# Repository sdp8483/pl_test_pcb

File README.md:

prototype circuits that dont warrent a seperate repo. Mostly undocumented, enter at your own risk!

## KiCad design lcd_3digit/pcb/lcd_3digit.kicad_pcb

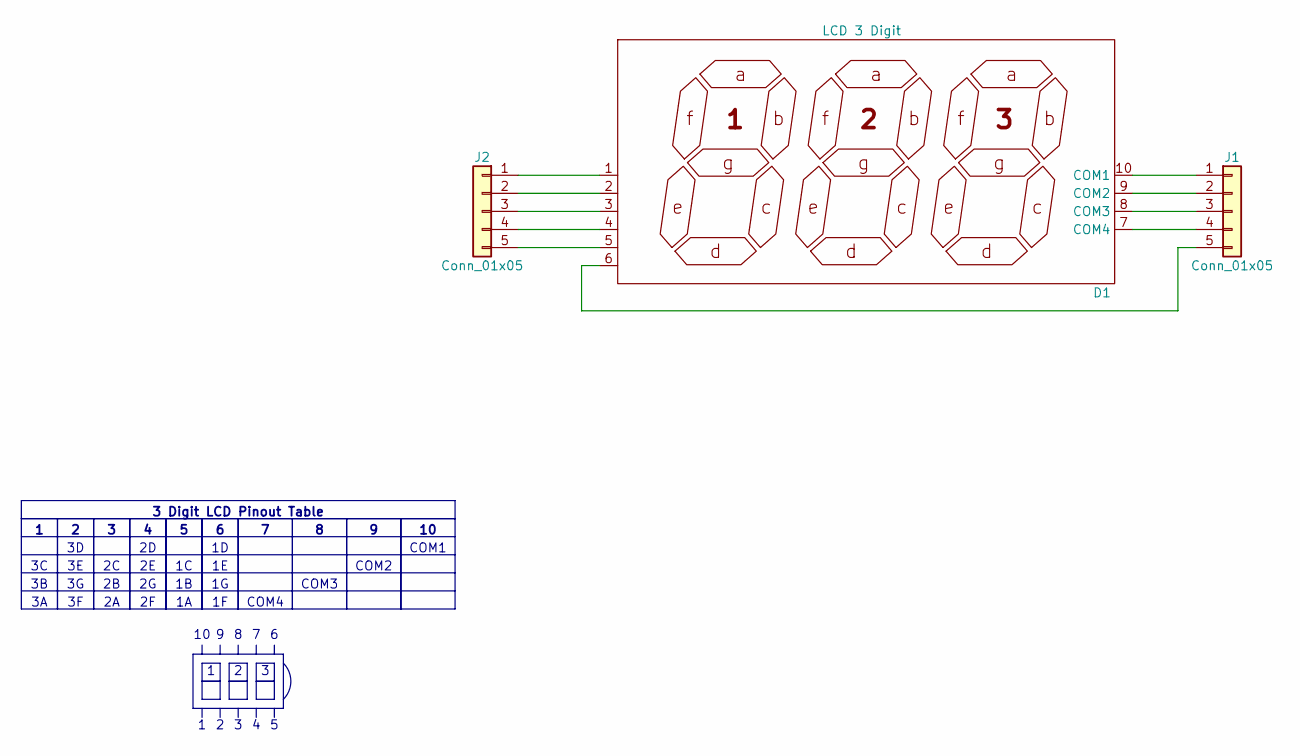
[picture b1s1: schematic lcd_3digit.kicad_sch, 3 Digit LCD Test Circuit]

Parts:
D1: LCD 3 Digit; LCD_3_Digit_10p
J1, J2: Conn_01x05; PinHeader_1x05_P2.54mm_Vertical

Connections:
unnamed: D1.10 (COM1), J1.1
unnamed: D1.9 (COM2), J1.2
unnamed: D1.8 (COM3), J1.3
unnamed: D1.7 (COM4), J1.4
unnamed: D1.6, J1.5
unnamed: D1.1, J2.1
unnamed: D1.2, J2.2
unnamed: D1.3, J2.3
unnamed: D1.4, J2.4
unnamed: D1.5, J2.5

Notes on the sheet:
COM1
COM3
COM2
COM4
3 Digit LCD Pinout Table

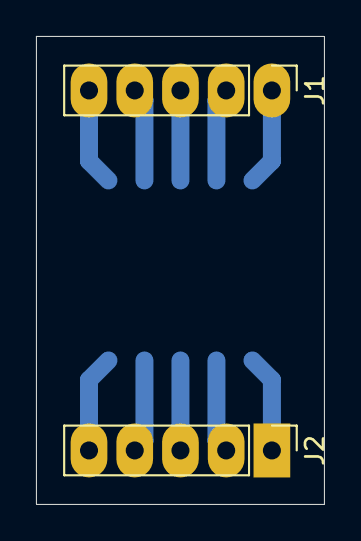
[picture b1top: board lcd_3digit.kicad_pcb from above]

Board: 2 copper layers, 16.0 x 26.0 mm, 3 parts (1 on the bottom side), 10 nets.

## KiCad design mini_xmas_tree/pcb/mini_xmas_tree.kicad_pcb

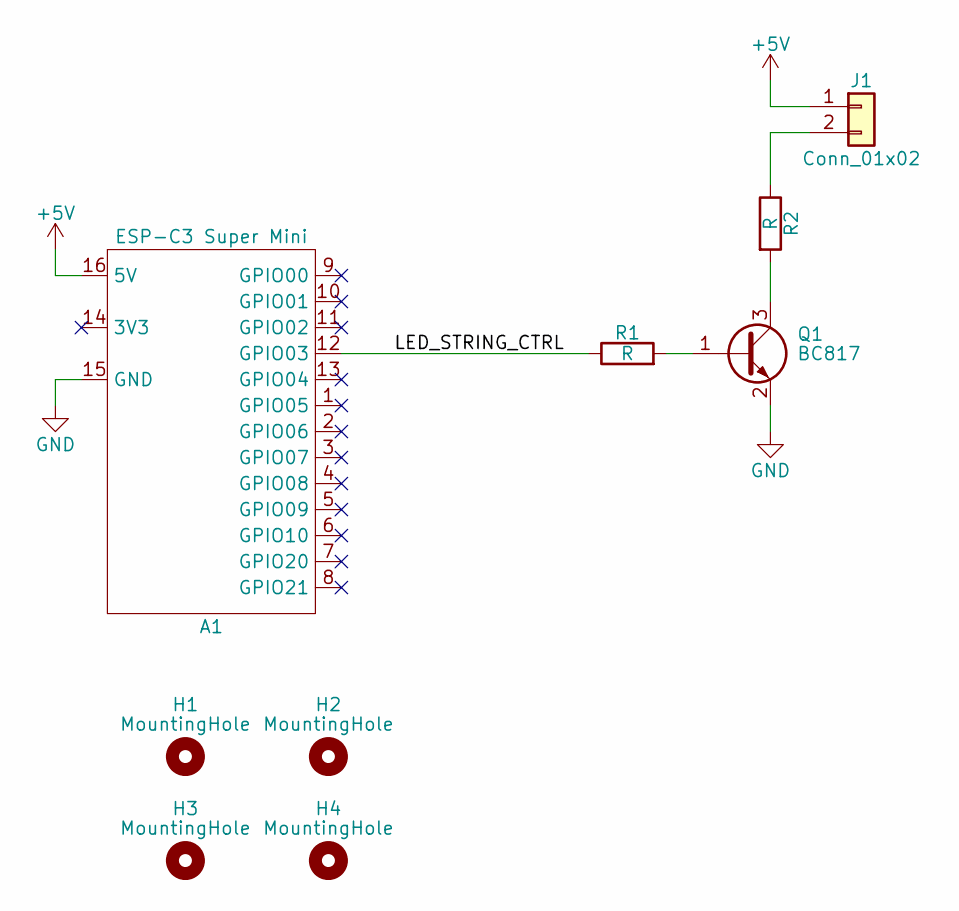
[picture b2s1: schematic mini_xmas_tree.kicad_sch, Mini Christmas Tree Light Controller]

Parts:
A1: ESP-C3 Super Mini; ESP32-C3 Super Mini
H1, H2, H3, H4: MountingHole; MountingHole_3.2mm_M3
J1: Conn_01x02; PinHeader_1x02_P2.54mm_Vertical
Q1: BC817; SOT-23
R1, R2: R; R_0805_2012Metric_Pad1.20x1.40mm_HandSolder

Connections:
+5V: A1.16 (5V), J1.1
/LED_STRING_CTRL: A1.12 (GPIO03), R1.1
GND: A1.15 (GND), Q1.2 (E)
unnamed: J1.2, R2.1
unnamed: Q1.1 (B), R1.2
unnamed: Q1.3 (C), R2.2

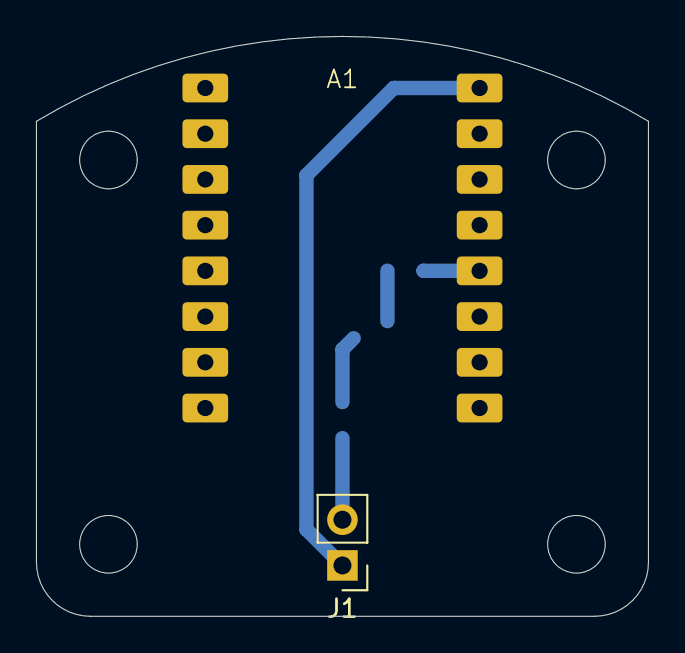
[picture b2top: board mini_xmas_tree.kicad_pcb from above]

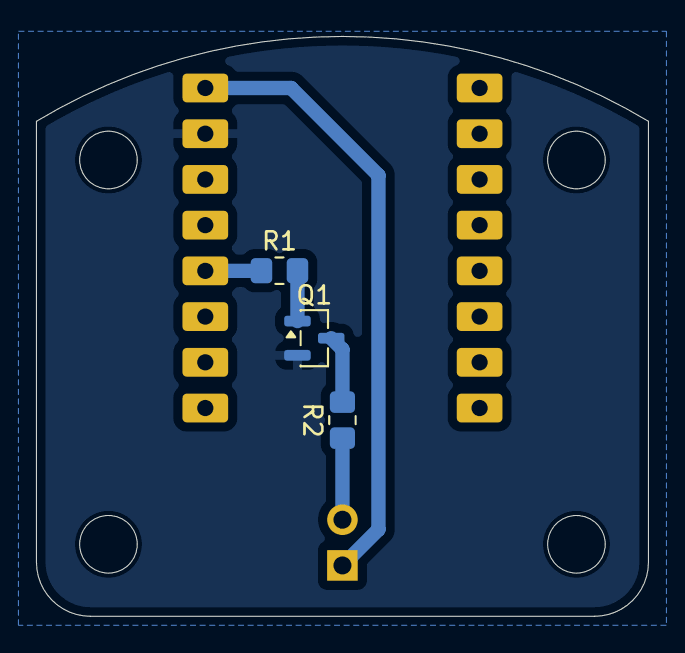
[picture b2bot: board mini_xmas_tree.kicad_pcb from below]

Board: 2 copper layers, 34.0 x 32.2 mm, 9 parts (3 on the bottom side), 6 nets.

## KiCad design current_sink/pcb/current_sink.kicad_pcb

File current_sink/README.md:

# CNC Milled PCB Project Template

Directory structure for starting a milled PCB project. 
Originally based off Hackaday article: https://hackaday.com/2017/05/18/kicad-best-practises-library-management/

## Directory Outline
- [`~/firmware/`](firmware): firmware source code and binaries.
- [`~/mechanical/`](mechanical): mechanical CAD design files, for example the enclosure.
    - [`~/mechanical/3d_files/`](mechanical/3d_files): files exported from CAD for import into 3D printer slicing software.
- [`~/pcb/`](pcb): KiCAD design files. When starting a new KiCAD project in this directory be sure to uncheck *Create a new directory for the project* in the **Create New Project** window.
    - [`/pcb/3d_models`](pcb/3d_models)

## Test

```bash
.
├── firmware
├── LICENSE
├── mechanical
│   └── 3d_files
├── pcb
│   ├── 3d_models
│   │   └── README.md
│   ├── bom
│   │   └── README.md
│   ├── datasheets
│   │   └── README.md
│   ├── gerber
│   │   └── README.md
│   ├── images
│   │   └── README.md
│   ├── lib_fp
│   │   ├── bb_logo.pretty
│   │   │   ├── BB_logo_HxW_4x7.5mm.kicad_mod
│   │   │   ├── BB_logo_HxW_5x9.4mm.kicad_mod
│   │   │   ├── BB_logo_HxW_6x11.3mm.kicad_mod
│   │   │   ├── BlueBirdLogo.png
│   │   │   └── BlueBirdLogo.xcf
│   │   ├── pl_logo.pretty
│   │   │   ├── logo_height_10mm.kicad_mod
│   │   │   ├── logo_height_15mm.kicad_mod
│   │   │   ├── logo_height_20mm.kicad_mod
│   │   │   ├── logo_height_3mm.kicad_mod
│   │   │   ├── logo_height_4mm.kicad_mod
│   │   │   ├── logo_height_5mm.kicad_mod
│   │   │   ├── logo_height_6mm.kicad_mod
│   │   │   ├── logo_height_7mm.kicad_mod
│   │   │   ├── logo_height_8mm.kicad_mod
│   │   │   └── logo_height_9mm.kicad_mod
│   │   └── README.md
│   ├── lib_sch
│   │   └── README.md
│   ├── page_layout
│   │   ├── pl_logo.kicad_wks
│   │   ├── pl_page_layout.kicad_wks
│   │   └── README.md
│   ├── pcb_render
│   │   └── README.md
│   └── schematic_pdf
│       └── README.md
└── README.md
```

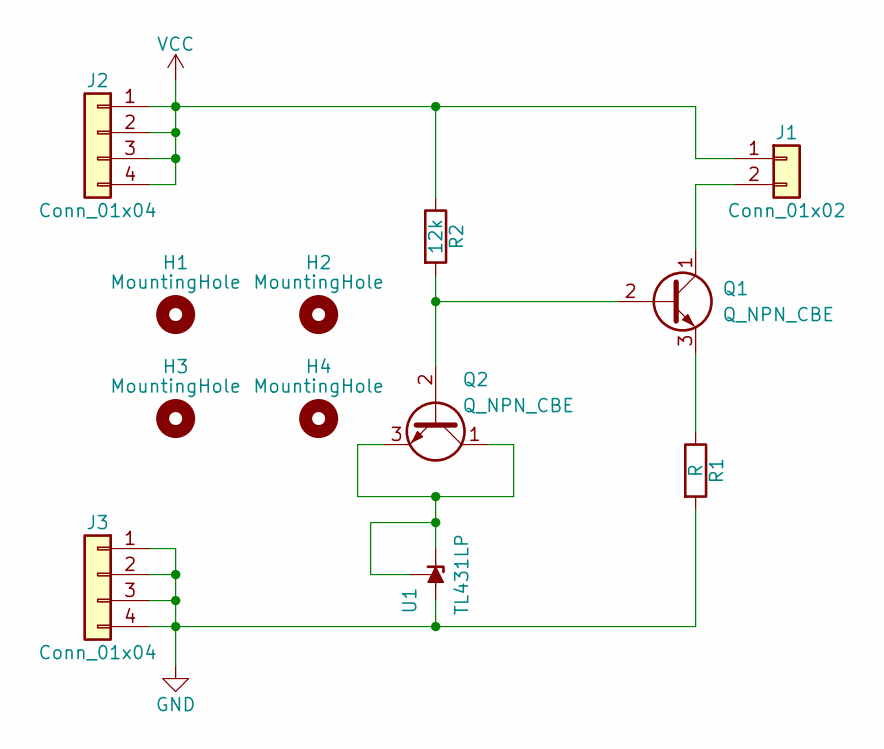
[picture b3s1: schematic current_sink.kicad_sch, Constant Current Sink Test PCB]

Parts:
H1, H2, H3, H4: MountingHole; MountingHole_3.2mm_M3
J1: Conn_01x02; PinHeader_1x02_P2.54mm_Vertical
J2, J3: Conn_01x04; PinHeader_1x04_P2.54mm_Vertical
Q1, Q2: Q_NPN_CBE; TO-92_Wide
R1: R; R_Axial_DIN0207_L6.3mm_D2.5mm_P10.16mm_Horizontal
R2: 12k; R_Axial_DIN0207_L6.3mm_D2.5mm_P10.16mm_Horizontal
U1: TL431LP; TO-92_Wide

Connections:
GND: J3.1, J3.2, J3.3, J3.4, R1.2, U1.2 (A)
unnamed: J1.2, Q1.1 (C)
unnamed: Q1.2 (B), Q2.2 (B), R2.2
unnamed: Q1.3 (E), R1.1
unnamed: Q2.1 (C), Q2.3 (E), U1.1 (REF), U1.3 (K)
VCC: J1.1, J2.1, J2.2, J2.3, J2.4, R2.1

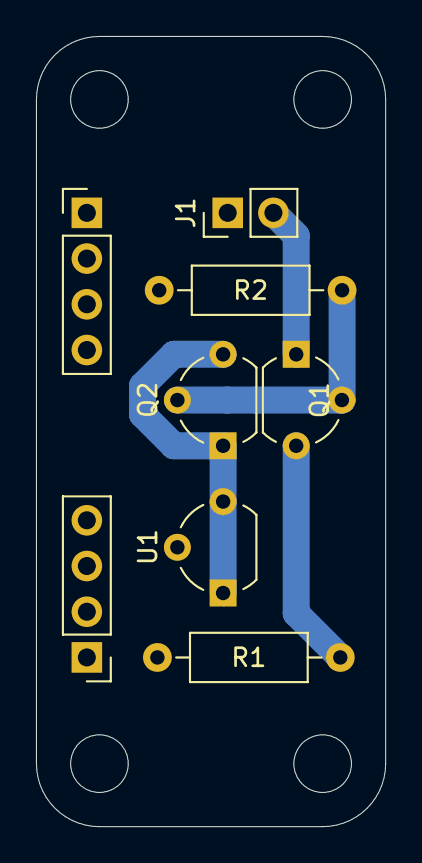
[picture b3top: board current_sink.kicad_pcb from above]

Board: 2 copper layers, 19.4 x 43.9 mm, 12 parts (0 on the bottom side), 6 nets.

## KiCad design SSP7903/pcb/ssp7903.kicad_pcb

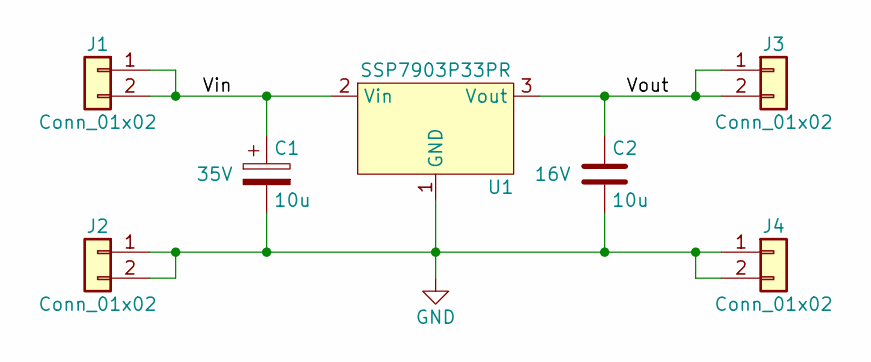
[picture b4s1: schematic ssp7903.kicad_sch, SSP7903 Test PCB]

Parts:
C1: 10u; CP_Radial_D5.0mm_P2.00mm; Voltage 35V
C2: 10u; C_1210_3225Metric_Pad1.33x2.70mm_HandSolder; Voltage 16V
J1, J2, J3, J4: Conn_01x02; PinHeader_1x02_P2.54mm_Vertical
U1: SSP7903P33PR; SOT-89-3

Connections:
/Vin: C1.1, J1.1, J1.2, U1.2 (Vin)
/Vout: C2.1, J3.1, J3.2, U1.3 (Vout)
GND: C1.2, C2.2, J2.1, J2.2, J4.1, J4.2, U1.1 (GND)

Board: 2 copper layers, 7 parts (2 on the bottom side), 3 nets, no tracks yet.

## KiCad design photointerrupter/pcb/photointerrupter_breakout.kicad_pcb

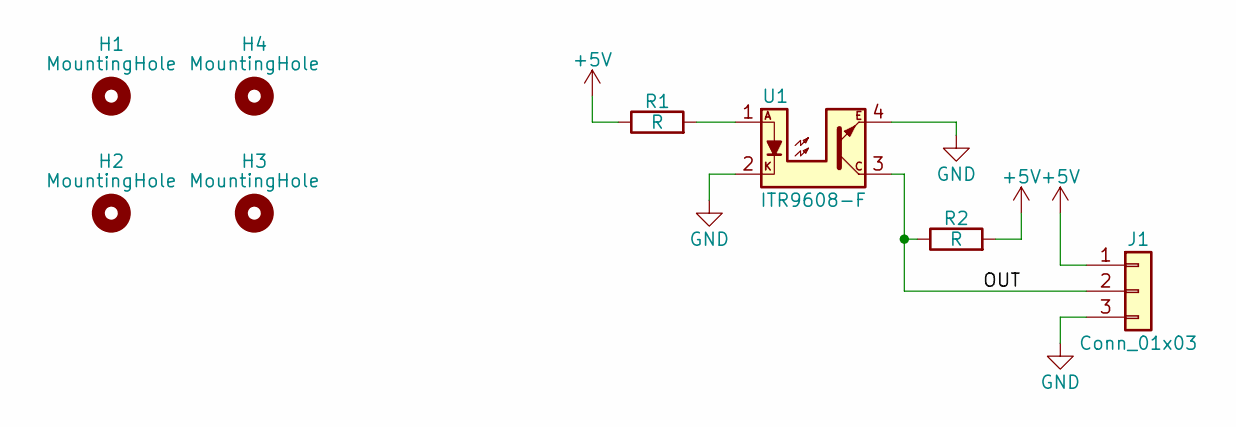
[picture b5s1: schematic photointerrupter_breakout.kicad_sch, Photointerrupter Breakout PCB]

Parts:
H1, H2, H3, H4: MountingHole; MountingHole_3.2mm_M3
J1: Conn_01x03; mill_PinHeader_1x03_P2.54mm_Vertical
R1, R2: R; R_0603_1608Metric_Pad0.98x0.95mm_HandSolder
U1: ITR9608-F; Everlight_ITR9608-F

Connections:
+5V: J1.1, R1.1, R2.2
/OUT: J1.2, R2.1, U1.3
GND: J1.3, U1.2, U1.4
unnamed: R1.2, U1.1

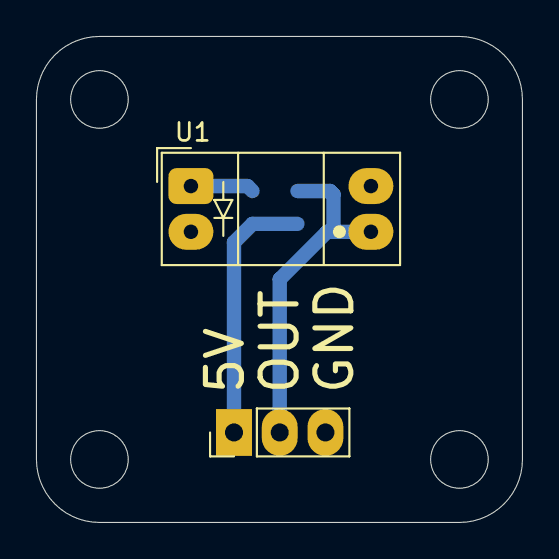
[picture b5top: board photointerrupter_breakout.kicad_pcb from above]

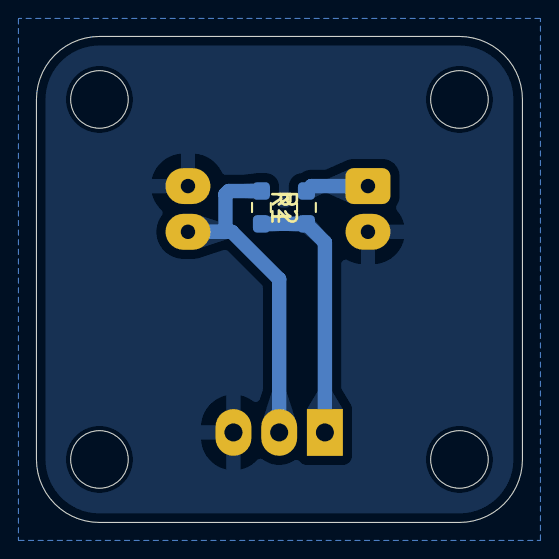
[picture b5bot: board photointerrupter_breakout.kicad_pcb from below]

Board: 2 copper layers, 27.0 x 27.0 mm, 8 parts (2 on the bottom side), 4 nets.

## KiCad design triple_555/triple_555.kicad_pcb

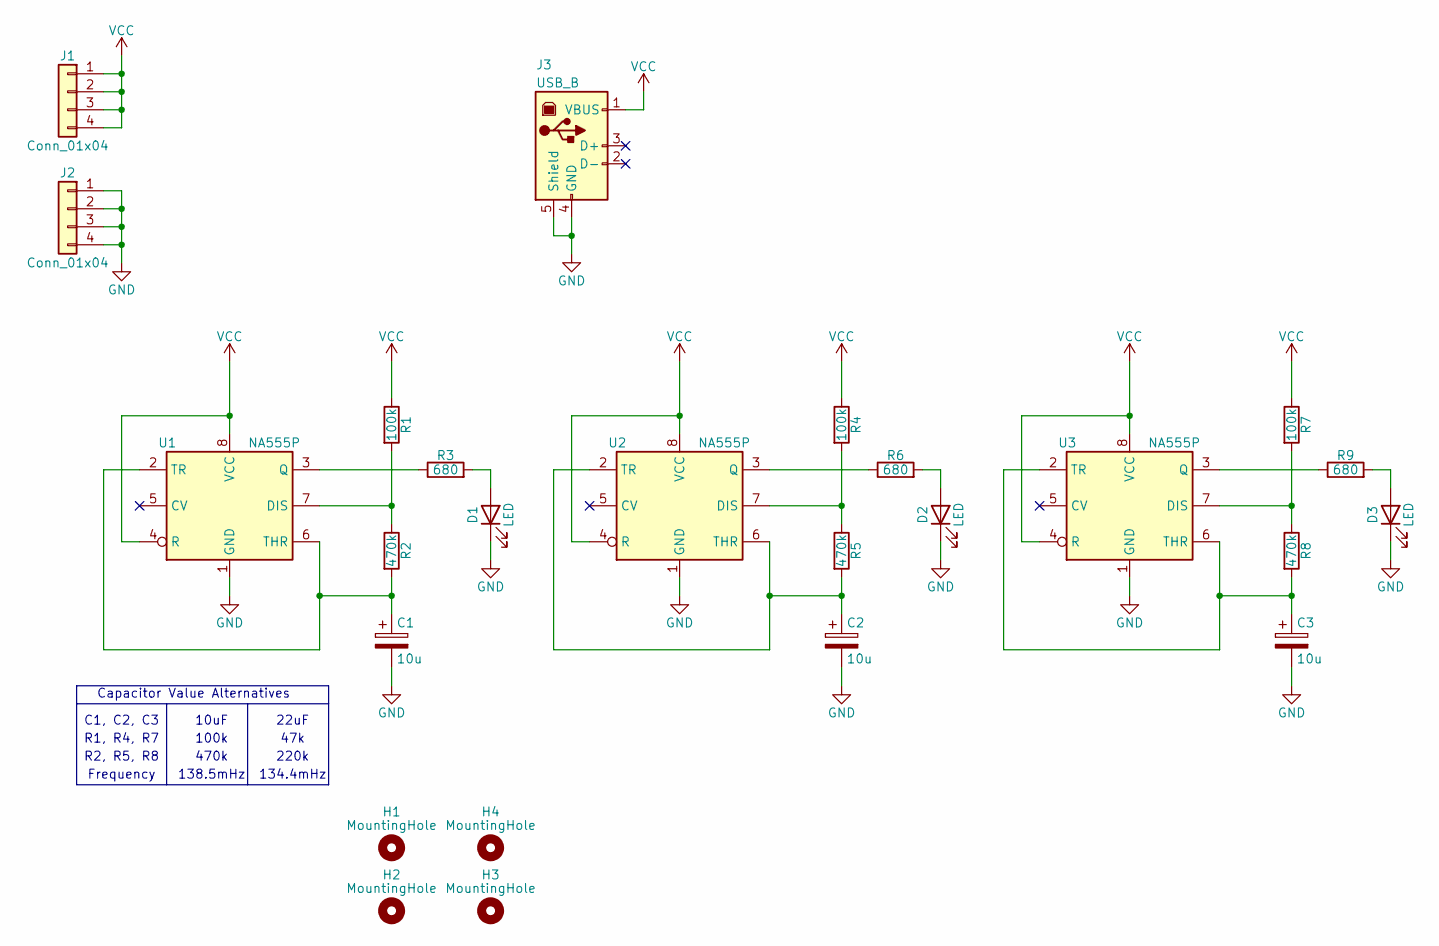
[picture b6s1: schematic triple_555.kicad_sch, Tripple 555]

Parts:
C1, C2, C3: 10u; CP_Radial_D5.0mm_P2.50mm
D1, D2, D3: LED; LED_D5.0mm
H1, H2, H3, H4: MountingHole; MountingHole_3.2mm_M3
J1, J2: Conn_01x04; PinHeader_1x04_P2.54mm_Vertical
J3: USB_B; USB_B_mill_spacing
R1, R4, R7: 100k; R_Axial_DIN0207_L6.3mm_D2.5mm_P10.16mm_Horizontal
R2, R5, R8: 470k; R_Axial_DIN0207_L6.3mm_D2.5mm_P10.16mm_Horizontal
R3, R6, R9: 680; R_Axial_DIN0207_L6.3mm_D2.5mm_P10.16mm_Horizontal
U1, U2, U3: NA555P; DIP-8_W7.62mm

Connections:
GND: C1.2, C2.2, C3.2, D1.1 (K), D2.1 (K), D3.1 (K), J2.1, J2.2, J2.3, J2.4, J3.4 (GND), J3.5 (Shield), U1.1 (GND), U2.1 (GND), U3.1 (GND)
unnamed: D1.2 (A), R3.2
unnamed: D2.2 (A), R6.2
unnamed: D3.2 (A), R9.2
unnamed: R1.2, R2.1, U1.7 (DIS)
unnamed: R3.1, U1.3 (Q)
unnamed: C1.1, R2.2, U1.2 (TR), U1.6 (THR)
unnamed: R4.2, R5.1, U2.7 (DIS)
unnamed: R6.1, U2.3 (Q)
unnamed: C2.1, R5.2, U2.2 (TR), U2.6 (THR)
unnamed: R7.2, R8.1, U3.7 (DIS)
unnamed: R9.1, U3.3 (Q)
unnamed: C3.1, R8.2, U3.2 (TR), U3.6 (THR)
VCC: J1.1, J1.2, J1.3, J1.4, J3.1 (VBUS), R1.1, R4.1, R7.1, U1.4 (R), U1.8 (VCC), U2.4 (R), U2.8 (VCC), U3.4 (R), U3.8 (VCC)

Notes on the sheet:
C1, C2, C3
138.5mHz
R2, R5, R8
Capacitor Value Alternatives
Frequency
220k
47k
22uF
134.4mHz
10uF
100k
470k
R1, R4, R7

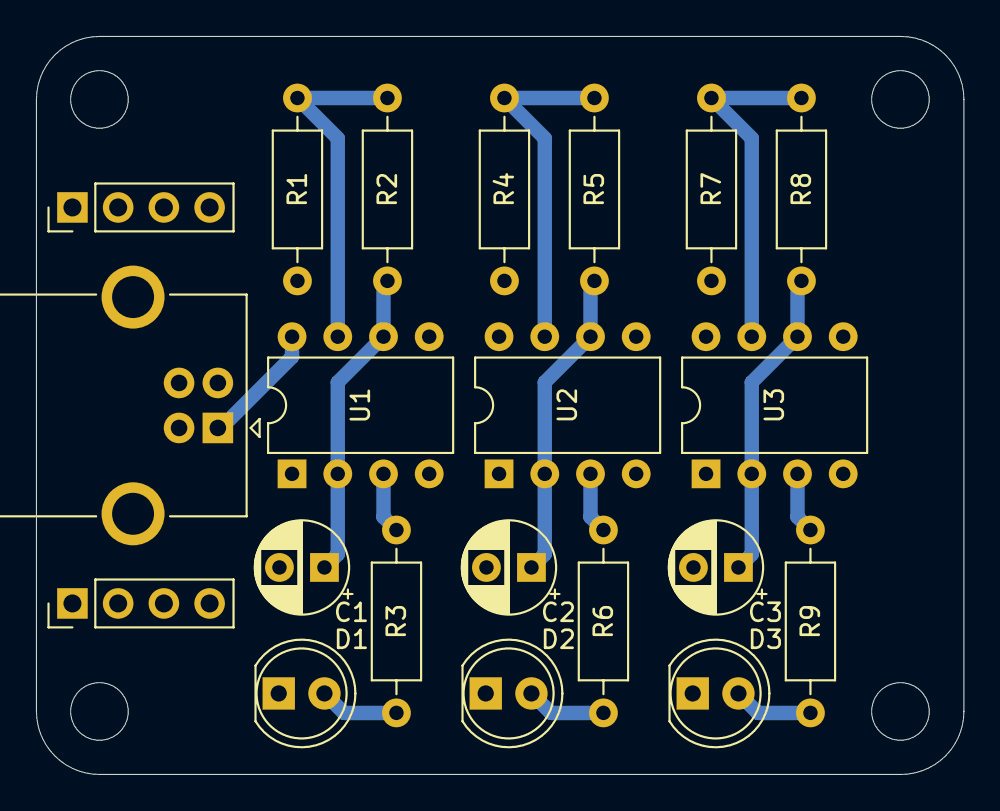
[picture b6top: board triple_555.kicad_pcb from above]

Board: 2 copper layers, 51.5 x 41.0 mm, 25 parts (0 on the bottom side), 14 nets.

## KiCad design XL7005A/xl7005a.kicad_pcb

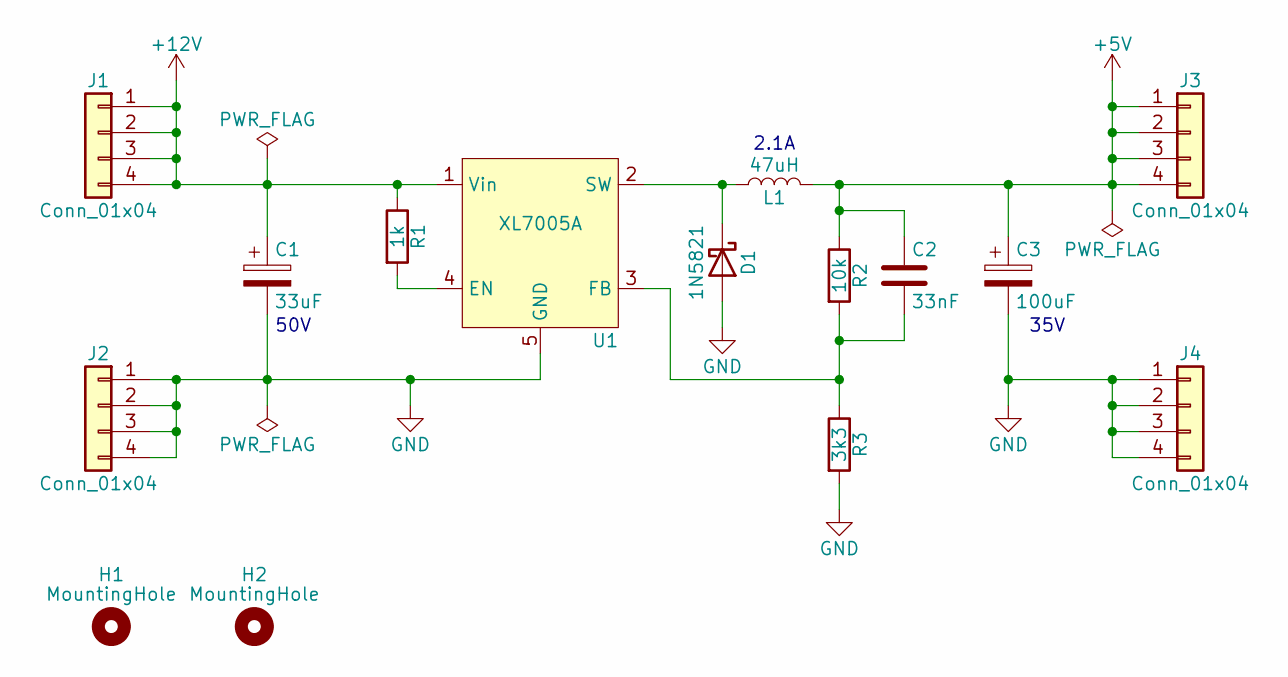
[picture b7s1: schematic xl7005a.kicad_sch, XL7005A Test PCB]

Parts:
C1: 33uF; CP_Axial_L18.0mm_D6.5mm_P25.00mm_Horizontal
C2: 33nF; C_Disc_D3.8mm_W2.6mm_P2.50mm
C3: 100uF; CP_Radial_D6.3mm_P2.50mm
D1: 1N5821; D_DO-201AD_P15.24mm_Horizontal
H1, H2: MountingHole; MountingHole_3.2mm_M3
J1, J2, J3, J4: Conn_01x04; PinHeader_1x04_P2.54mm_Vertical
L1: 47uH; L_10.4x10.4_H4.8
R1: 1k; R_Axial_DIN0207_L6.3mm_D2.5mm_P10.16mm_Horizontal
R2: 10k; R_Axial_DIN0207_L6.3mm_D2.5mm_P10.16mm_Horizontal
R3: 3k3; R_Axial_DIN0207_L6.3mm_D2.5mm_P10.16mm_Horizontal
U1: XL7005A; SOIC-8-1EP_3.9x4.9mm_P1.27mm_EP2.41x3.3mm

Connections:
+5V: C2.1, C3.1, J3.1, J3.2, J3.3, J3.4, L1.2, R2.1
+12V: C1.1, J1.1, J1.2, J1.3, J1.4, R1.1, U1.1 (Vin)
GND: C1.2, C3.2, D1.2 (A), J2.1, J2.2, J2.3, J2.4, J4.1, J4.2, J4.3, J4.4, R3.2, U1.5 (GND), U1.6 (GND), U1.7 (GND), U1.8 (GND), U1.9 (PAD)
unnamed: D1.1 (K), L1.1, U1.2 (SW)
unnamed: R1.2, U1.4 (EN)
unnamed: C2.2, R2.2, R3.1, U1.3 (FB)

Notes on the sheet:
50V
2.1A
35V

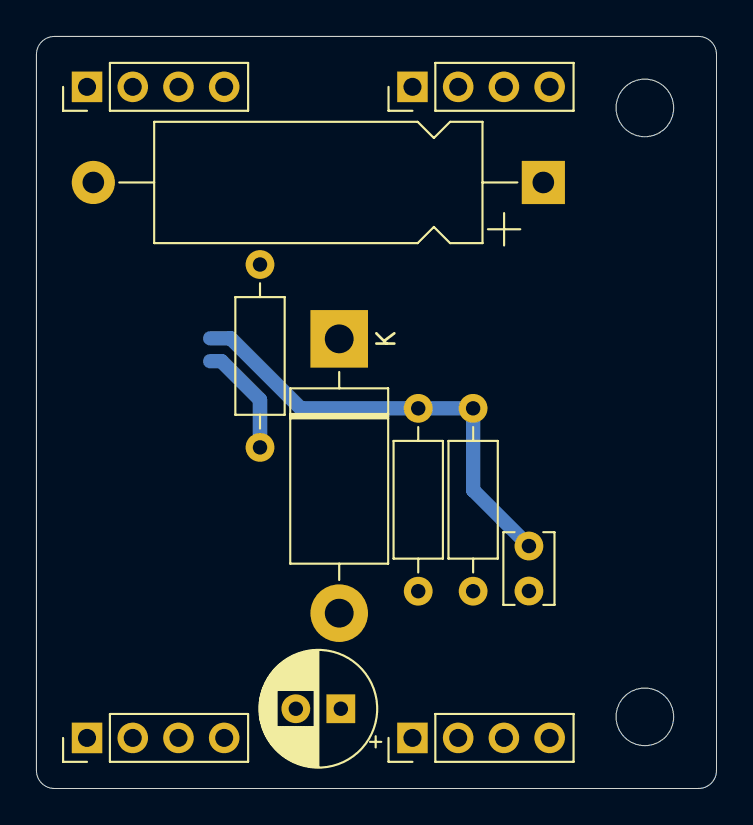
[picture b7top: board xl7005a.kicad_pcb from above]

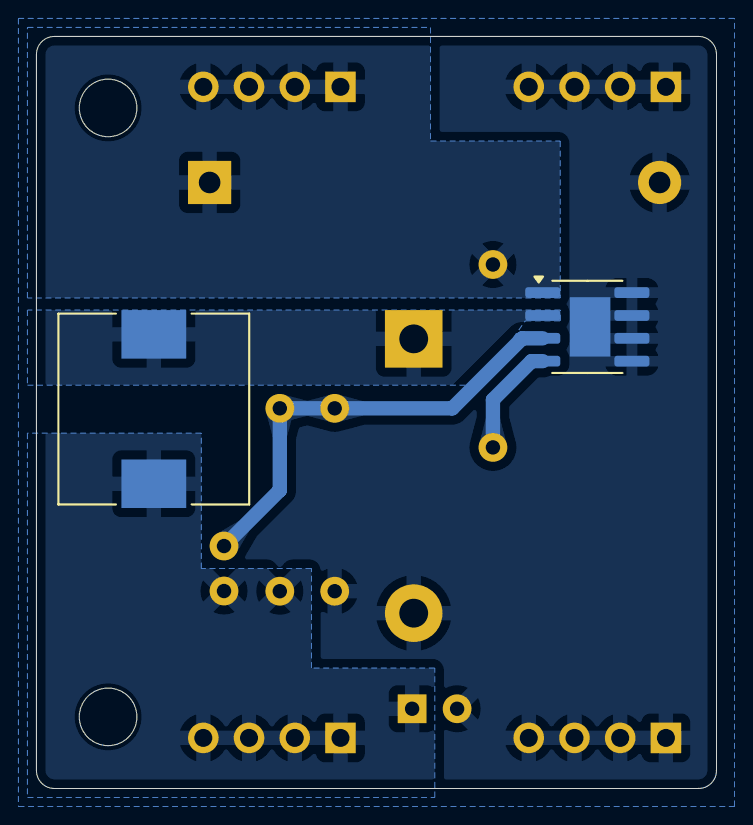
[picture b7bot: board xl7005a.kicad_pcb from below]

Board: 2 copper layers, 37.8 x 41.8 mm, 15 parts (2 on the bottom side), 6 nets.

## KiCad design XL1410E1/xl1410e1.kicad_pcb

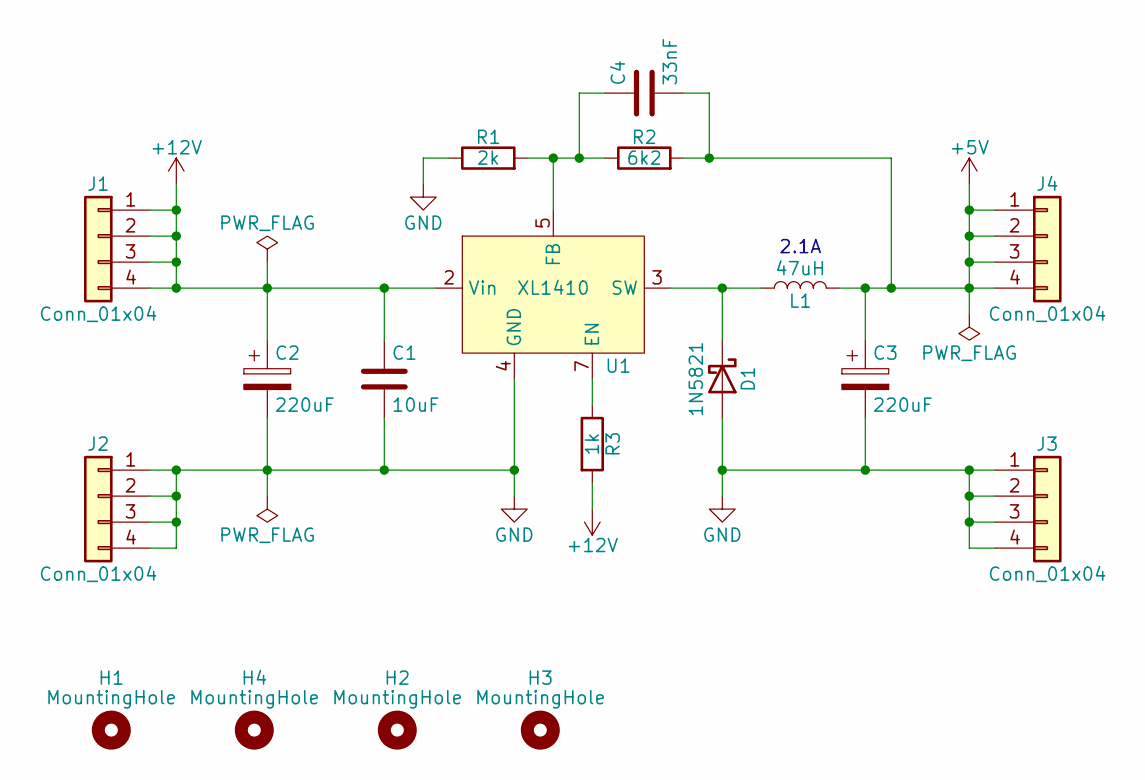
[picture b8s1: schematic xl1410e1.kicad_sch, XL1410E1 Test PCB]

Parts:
C1: 10uF; C_1206_3216Metric_Pad1.33x1.80mm_HandSolder
C2, C3: 220uF; CP_Radial_D10.0mm_P5.00mm
C4: 33nF; C_Disc_D3.8mm_W2.6mm_P2.50mm
D1: 1N5821; D_DO-201AD_P15.24mm_Horizontal
H1, H2, H3, H4: MountingHole; MountingHole_3.2mm_M3
J1, J2, J3, J4: Conn_01x04; PinHeader_1x04_P2.54mm_Vertical
L1: 47uH; L_10.4x10.4_H4.8
R1: 2k; R_Axial_DIN0207_L6.3mm_D2.5mm_P10.16mm_Horizontal
R2: 6k2; R_Axial_DIN0207_L6.3mm_D2.5mm_P10.16mm_Horizontal
R3: 1k; R_Axial_DIN0207_L6.3mm_D2.5mm_P10.16mm_Horizontal
U1: XL1410; SOIC-8_3.9x4.9mm_P1.27mm

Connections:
+5V: C3.1, C4.2, J4.1, J4.2, J4.3, J4.4, L1.2, R2.2
+12V: C1.1, C2.1, J1.1, J1.2, J1.3, J1.4, R3.2, U1.2 (Vin)
GND: C1.2, C2.2, C3.2, D1.2 (A), J2.1, J2.2, J2.3, J2.4, J3.1, J3.2, J3.3, J3.4, R1.1, U1.4 (GND)
unnamed: D1.1 (K), L1.1, U1.3 (SW)
unnamed: R3.1, U1.7 (EN)
unnamed: C4.1, R1.2, R2.1, U1.5 (FB)

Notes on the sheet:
2.1A

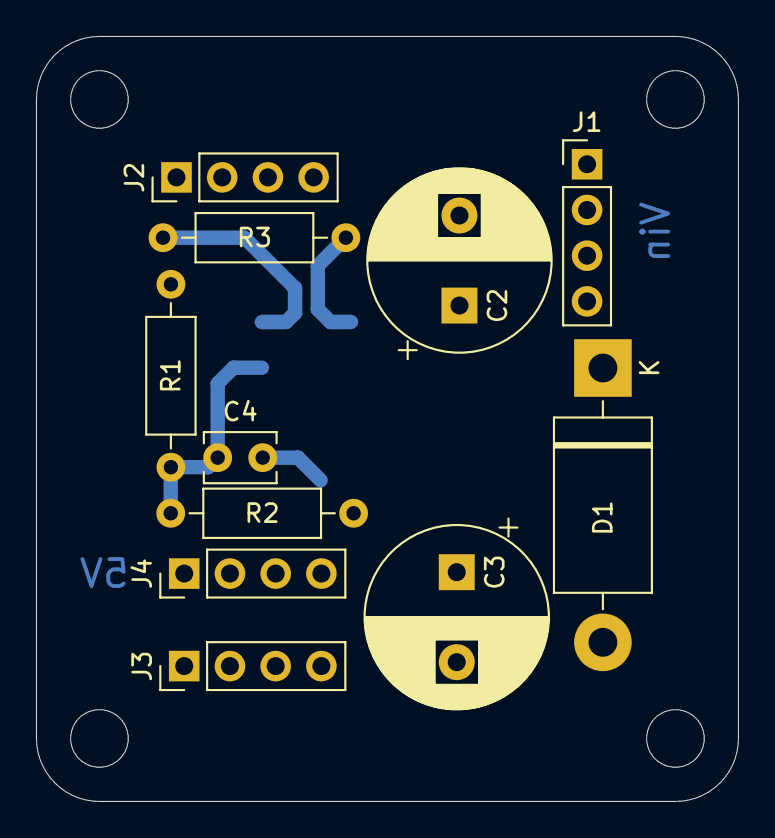
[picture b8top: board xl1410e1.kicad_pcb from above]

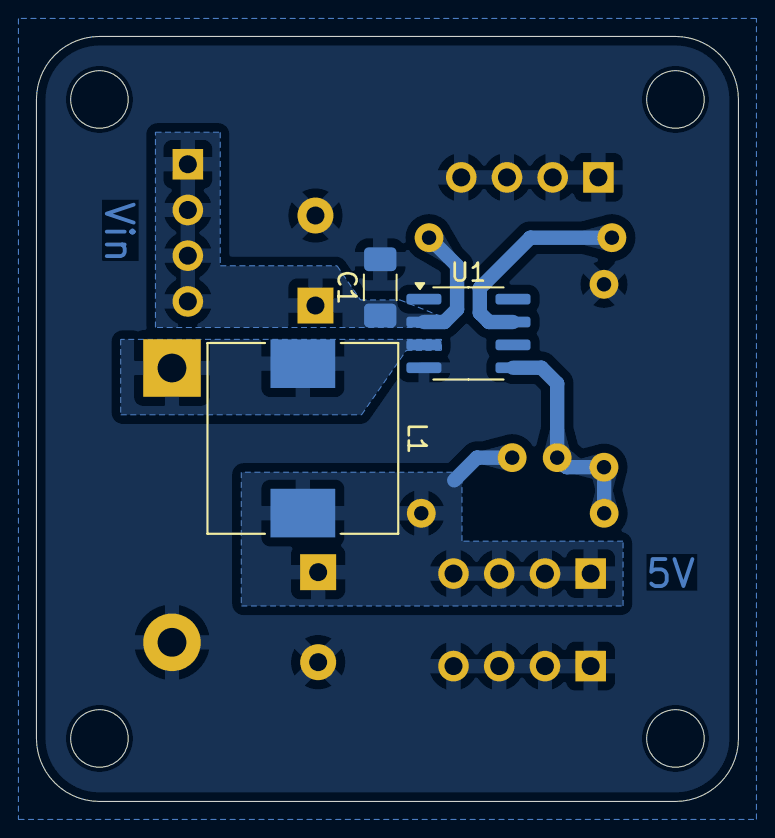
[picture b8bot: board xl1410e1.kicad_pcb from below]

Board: 2 copper layers, 39.0 x 42.5 mm, 18 parts (3 on the bottom side), 6 nets.

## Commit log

2024-03-22 init commit of LGS5145 circuit
2024-03-22 add ibom
2024-03-26 restructure dir
2024-03-27 create scanning script
2024-03-27 rename
2024-03-27 40vin data
2024-03-31 collect more data
2024-04-05 create dir
2024-04-05 create schema
2024-04-05 create breakout
2024-04-05 init blink code
2024-04-12 breakout UPDI
2024-04-13 init
2024-04-13 mill ready
2024-04-15 change xtal footprint to pin header
2024-04-20 init commit
2024-04-20 create all
2024-04-20 output schematic
2024-04-21 move to pcb dir
2024-04-21 create test pcb
2024-04-21 create ibom
2024-04-21 increase pin hole diameter
2024-04-21 increase bias current
2024-05-08 schematic capture
2024-05-09 pcb layout 1
2024-05-09 pcb gcode
2024-06-02 create schematic
2024-06-02 create fw
2024-06-13 export gerber
2024-06-13 Create millproject
2024-06-13 create gcode
2024-06-19 init kicad project
2024-06-24 init schma and layout
2024-06-25 change fbk resistor values
2024-06-25 output ibom
2024-11-22 create pcb layout
2024-11-23 add alt value table
2024-11-24 add usb b 3d model
2024-11-24 increase pin spacing for mill clearance
2024-11-24 add usb b connector
2024-11-24 update gerbers
2024-11-24 single depth cu removal
2024-11-24 increase vcc fill clearance
2024-11-24 export increased vcc clearance
2024-11-24 increase min width filled zones
2024-11-24 export updated gerbers
2024-11-24 generate updated gcode
2024-11-24 export schematic pdf
2024-11-24 set title
2024-11-24 resize table
2024-11-24 update page layout and title block
2024-11-24 update rev
2024-12-19 create pcb
2024-12-21 export BMask
2024-12-21 create back solder mask mill
2024-12-21 mill mask at z=0
2024-12-21 z must be non zero, set to small level
2025-03-08 rotate files
2025-12-02 start pcb layout
